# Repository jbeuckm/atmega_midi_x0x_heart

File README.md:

# MIDI interface for x0x heart

Atmega328 MIDI interface for the x0x heart http://www.openmusiclabs.com/projects/x0x-heart/

One-sided for easy home DIY.

### NOTE ON/OFF

The gate pins of the eurorack connector are raised to 5V during the note. The "CV" pins of the eurorack connector are set to 1V/oct pitch control voltage. A pitch scale trimpot can be used to tune the x0x.

### Continuous Controllers

| MIDI CC | Function                           |
| ------- | ---------------------------------- |
| 1       | Envelope                           |
| 2       | Resonance                          |
| 11      | Accent                             |
| 65      | Slide above 64 / No slide below 64 |
| 70      | Saw level                          |
| 71      | Square level                       |
| 72      | Decay                              |
| 74      | VCF Cutoff                         |

### System Exclusive

MIDI Sysex messages for this device begin with a four-byte prefix of the Sysex status byte, manufacturer ID, model ID and device ID.

`F0` sysex start

`77 33` manufacturer ID, model ID

`xx` device ID as set by trim pot

--

#### Set MIDI Channel

At startup, the MIDI channel of the device is the same as the device ID set with the trim pot.

A seven-byte sysex message can be used to change the channel of the interface.

`F0 77 33 xx` sysex prefix

`00` select MIDI channel parameter

`xx` new MIDI channel (0 for omni)

`F7` end of message

--

#### Patch Dump Request

A six-byte sysex message can be used to request a dump of the current voice parameters.

`F0 77 33 xx` sysex prefix

`01` patch dump request

`F7` end of message

The interface will then send a patch dump sysex message that encodes the current voice parameter values.

`F0 77 33 xx` sysex prefix

`02` patch dump

`ee rr aa pp ss qq dd ff`

envelope, resonance, accent, slide, saw, square, decay, cutoff (eight bytes)

`F7` end of message

This dumped patch data can be used to set all voice parameters by sending it back to the interface.

--

#### Save Patch

`F0 77 33 xx` sysex prefix

`11` save patch

`pp` patch number (0-127)

`F7` end of message

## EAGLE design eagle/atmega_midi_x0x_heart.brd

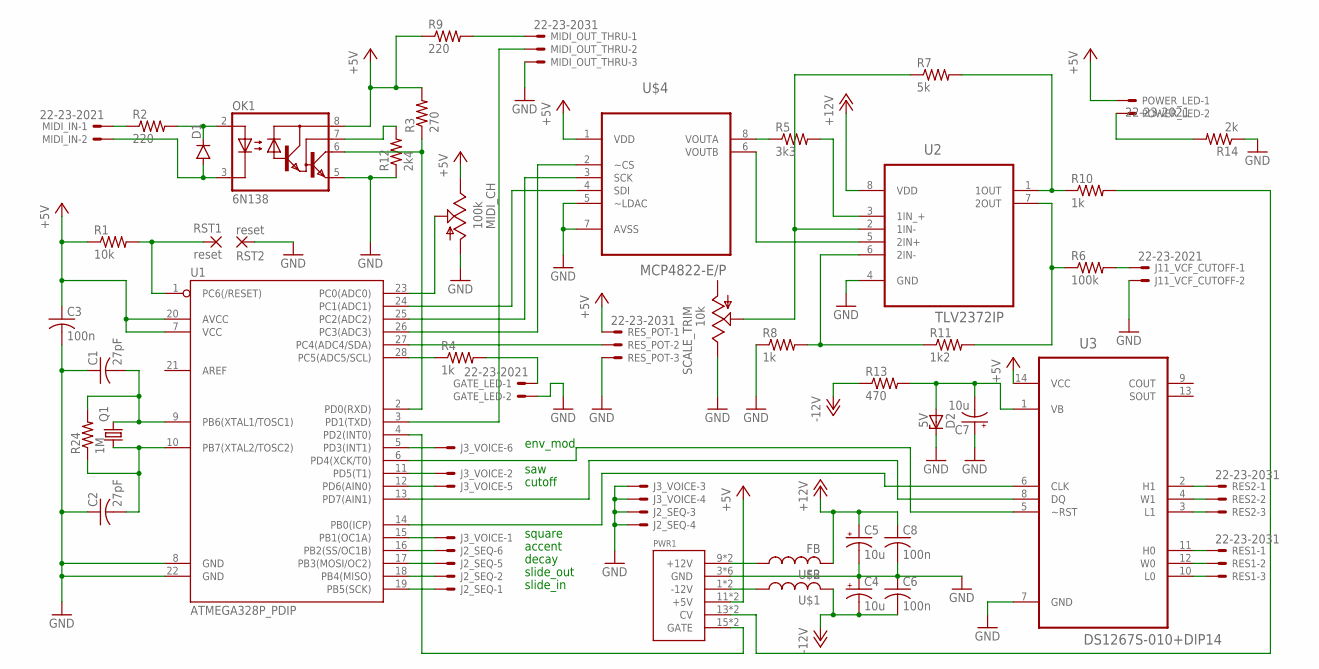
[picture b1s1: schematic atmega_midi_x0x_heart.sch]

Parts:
C1, C2: 27pF; C050-024X044
C3, C6, C8: 100n; C050-024X044
C4, C5: 10u; B45181A
C7: 10u; B45181B
D1: DIODE1N4148; DIODE-1N4148
D2: 5V; DO35Z10
GATE_LED: 22-23-2021
J2_SEQ, J3_VOICE: 22-23-2061
J11_VCF_CUTOFF: 22-23-2021
MIDI_CH: 100k; B64W
MIDI_IN: 22-23-2021
MIDI_OUT_THRU: 22-23-2031
OK1: 6N138; DIL08
POWER_LED: 22-23-2021
PWR1: POWER; POWER_16
Q1: CRYSTALHC49S; HC49/S
R1: 10k; 0207/10
R2, R9: 220; 0207/10
R3: 270; 0207/10
R4, R8, R10: 1k; 0207/10
R5: 3k3; 0207/10
R6: 100k; 0207/10
R7: 5k; 0207/10
R11: 1k2; 0207/10
R12: 2k4; 0207/10
R13: 470; 0207/10
R14: 2k; 0207/10
R24: 1M; 0207/10
RES1, RES2: 22-23-2031
RES_POT: 22-23-2031
RST1, RST2: reset; 2,54/0,9
SCALE_TRIM: 10k; B64W
U1: ATMEGA328P_PDIP; DIL28-3
U2: TLV2372IP; DIP254P762X508-8
U3: DS1267S-010+DIP14; DIP14
U$1, U$2: FB
U$4: MCP4822-E/P; DIP254P762X432-8

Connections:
+5V: C3.1, MIDI_CH.E, OK1.8 (VCC), POWER_LED.1, PWR1.11 (+5V), PWR1.12 (+5V), R1.1, R3.2, R9.1, RES_POT.1, U1.7 (VCC), U1.20 (AVCC), U3.14 (VCC), U$4.1 (VDD)
+12V: C5.+, C8.1, U2.8 (VDD), U$2.P$2 (2)
-12V: C4.-, C6.2, R13.1, U$1.P$2 (2)
GND: C1.1, C2.1, C3.2, C4.+, C5.-, C6.1, C7.+, C8.2, D2.C, GATE_LED.2, J2_SEQ.3, J2_SEQ.4, J3_VOICE.3, J3_VOICE.4, J11_VCF_CUTOFF.2, MIDI_CH.A, MIDI_OUT_THRU.3, OK1.5 (GND), PWR1.3 (GND), PWR1.4 (GND), PWR1.5 (GND), PWR1.6 (GND), PWR1.7 (GND), PWR1.8 (GND), R8.1, R12.1, R14.1, RES_POT.3, RST2.1, SCALE_TRIM.E, U1.8 (GND), U1.22 (GND), U2.4 (GND), U3.7 (GND), U$4.5 (~LDAC), U$4.7 (AVSS)
unnamed: J3_VOICE.6, U1.5 (PD3(INT1))
unnamed: R5.1, U$4.8 (VOUTA)
unnamed: D1.A, MIDI_IN.2, OK1.3 (C)
unnamed: C1.2, Q1.2, R24.2, U1.9 (PB6(XTAL1/TOSC1))
unnamed: C2.2, Q1.1, R24.1, U1.10 (PB7(XTAL2/TOSC2))
unnamed: R5.2, U2.3 (1IN_+)
unnamed: D1.C, OK1.2 (A), R2.2
unnamed: MIDI_IN.1, R2.1
unnamed: J3_VOICE.1, U1.15 (PB1(OC1A))
unnamed: J3_VOICE.2, U1.11 (PD5(T1))
unnamed: PWR1.9 (+12V), PWR1.10 (+12V), U$2.P$1 (1)
unnamed: R7.1, SCALE_TRIM.S, U2.2 (1IN-)
unnamed: R8.2, R11.1, U2.6 (2IN-)
unnamed: U2.5 (2IN+), U$4.6 (VOUTB)
unnamed: PWR1.13 (CV), PWR1.14 (CV), R10.2
unnamed: J3_VOICE.5, U1.12 (PD6(AIN0))
unnamed: R6.1, R11.2, U2.7 (2OUT)
unnamed: J2_SEQ.1, U1.19 (PB5(SCK))
unnamed: MIDI_CH.S, U1.23 (PC0(ADC0))
unnamed: J2_SEQ.2, U1.18 (PB4(MISO))
unnamed: J2_SEQ.5, U1.17 (PB3(MOSI/OC2))
unnamed: U1.6 (PD4(XCK/T0)), U3.5 (~RST)
unnamed: J2_SEQ.6, U1.16 (PB2(SS/OC1B))
unnamed: GATE_LED.1, R4.2
unnamed: U1.25 (PC2(ADC2)), U$4.3 (SCK)
unnamed: U1.24 (PC1(ADC1)), U$4.4 (SDI)
unnamed: R7.2, R10.1, U2.1 (1OUT)
unnamed: R4.1, U1.28 (PC5(ADC5/SCL))
unnamed: J11_VCF_CUTOFF.1, R6.2
unnamed: OK1.6 (VO), R3.1, U1.2 (PD0(RXD))
unnamed: RES2.2, U3.4 (W1)
unnamed: RES2.1, U3.2 (H1)
unnamed: RES2.3, U3.3 (L1)
unnamed: RES1.2, U3.12 (W0)
unnamed: RES1.1, U3.11 (H0)
unnamed: RES1.3, U3.10 (L0)
unnamed: U1.14 (PB0(ICP)), U3.6 (CLK)
unnamed: RES_POT.2, U1.27 (PC4(ADC4/SDA))
unnamed: MIDI_OUT_THRU.1, R9.2
unnamed: PWR1.15 (GATE), PWR1.16 (GATE), U1.4 (PD2(INT0))
unnamed: U1.13 (PD7(AIN1)), U3.8 (DQ)
unnamed: MIDI_OUT_THRU.2, U1.3 (PD1(TXD))
unnamed: R1.2, RST1.1, U1.1 (PC6(/RESET))
unnamed: OK1.7 (VB), R12.2
unnamed: U1.26 (PC3(ADC3)), U$4.2 (~CS)
unnamed: POWER_LED.2, R14.2
unnamed: PWR1.1 (-12V), PWR1.2 (-12V), U$1.P$1 (1)
unnamed: C7.-, D2.A, R13.2, U3.1 (VB)

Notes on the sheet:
square
saw
cutoff
env_mod
slide_in
slide_out
decay
accent

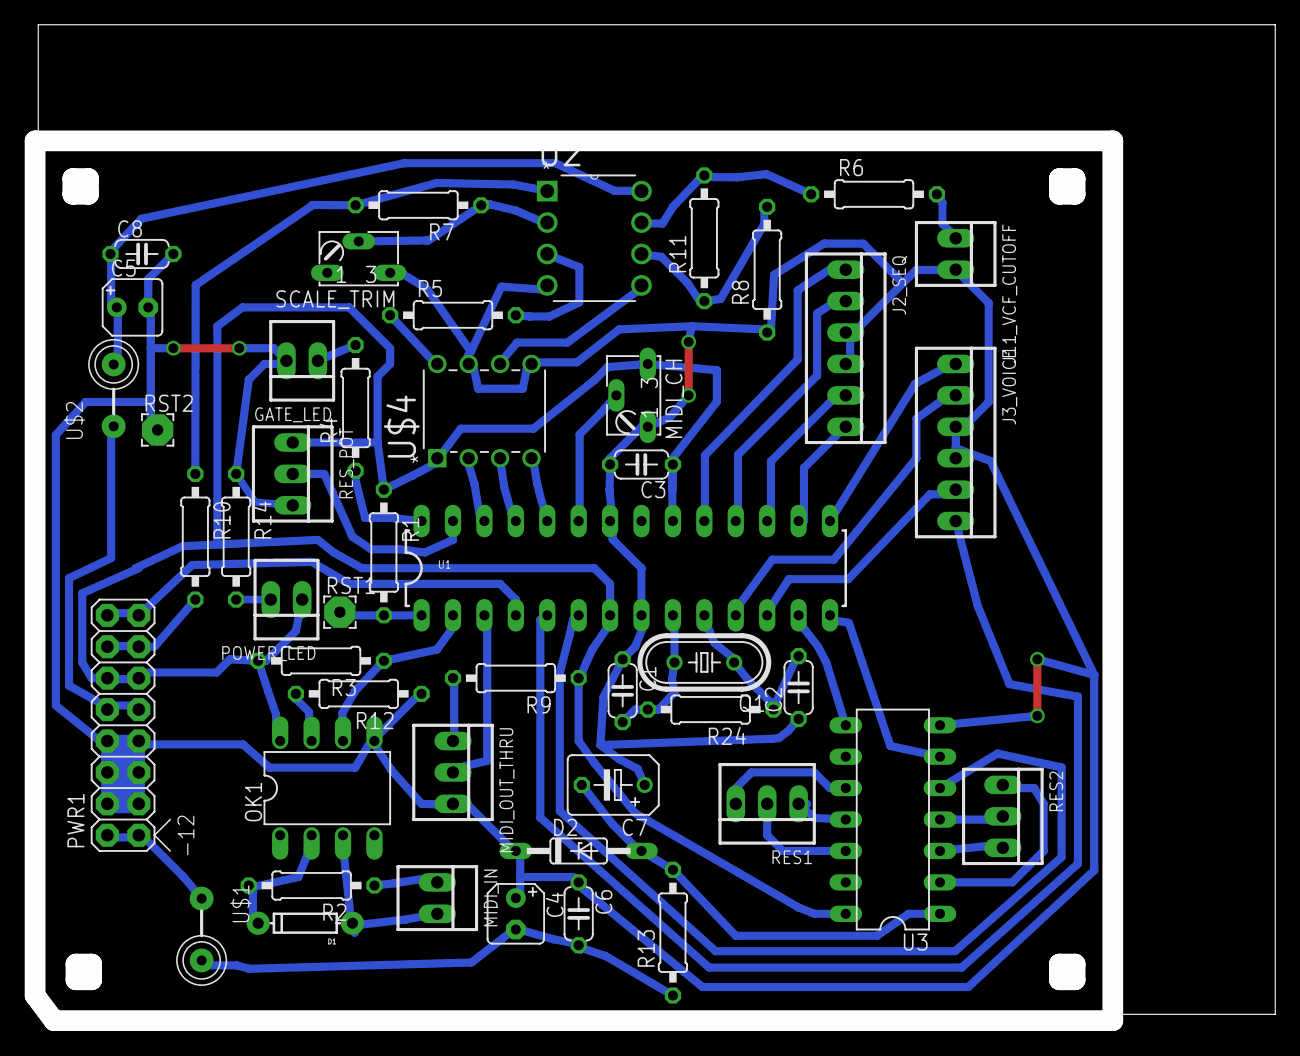
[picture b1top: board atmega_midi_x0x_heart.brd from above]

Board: 2 copper layers, 99.4 x 79.7 mm, 48 parts (0 on the bottom side), 52 nets.

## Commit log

2016-02-11 working up schemo
2016-02-12 pwm pins connected in schemo
2016-02-12 niced up schemo
2016-02-13 started up the layout
2016-02-13 pretty good positioning
2016-02-13 rebuilt brd with redone gnd
2016-02-13 nearly routed
2016-02-13 routed
2016-02-13 setting up pin constants and added gate led
2016-02-14 pin and midi controller number constants
2016-02-14 gcode
2016-02-14 initializing outputs
2016-02-15 fixed touching trace
2016-02-15 moved J2 away from midi channel trim
2016-02-15 changed env mod to ctrl 1
2016-02-15 configured timers for faster-than-sound PWM
2016-02-16 brd tweaks
2016-02-25 added vcf output resistor
2016-03-06 disabling interrupts during midi and more permissive gate on condition
2016-03-07 removed ineffectual cli calls and audible play scale timing
2016-03-09 changed to TI precision opamp
2016-03-09 tweaked cutout for better holes
2016-03-09 digital pot and midi out
2016-03-09 initial layout for res control version
2016-03-09 brd drc
2016-03-10 layout tweaks
2016-03-10 97 pct autorouted
2016-03-10 switched gate and pot ctrl pins for positioning
2016-03-10 almost
2016-03-11 cutout
2016-03-13 ready to cut
2016-03-16 ds1267 is there
2016-03-16 power led
2016-03-16 leds converted to connectors
2016-03-16 schemo tweaks
2016-03-16 readme
2016-03-16 fancy markdown table
2016-03-16 high 80s autoroute
2016-03-17 using molex friction parts
2016-03-17 90pct auto
2016-03-17 possibly routed
2016-03-17 board tweaks
2016-03-19 tweaks and cutout
2016-03-27 corrected midi led pin and built prototype produces gate led correctly
2016-03-27 starting a class to talk to the digipot
2016-03-28 digipot code ready to try
2016-03-29 instantiated digipot object
2016-03-29 digipot library compiles
2016-04-05 reversed resonance and fixed a couple of pins
2016-04-16 resonance from either onboard knob or midi
2016-07-18 cleanup and dac code included
2016-07-19 starting sysex doc
2016-07-19 more docs and patch dump code
2016-07-19 sysex dump request and dump receive work
2016-10-20 setting VCF CV with controller instead of velocity and no PWM VCF
2017-02-22 adding patch saving and retrieving
2017-02-22 added ruler to readme
2017-04-16 midi device paqnel for cubase
2019-11-23 layout pic
2019-11-27 set high PWM freq before setPinMode() and accent when velocity > 100

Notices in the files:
parts and their libraries:
SparkFun-DiscreteSemi: Licensing: Creative Commons ShareAlike 4.0 International - https://creativecommons.org/licenses/by-sa/4.0
